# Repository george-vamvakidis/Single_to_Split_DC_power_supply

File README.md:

# Single_to_Split_DC_power_supply

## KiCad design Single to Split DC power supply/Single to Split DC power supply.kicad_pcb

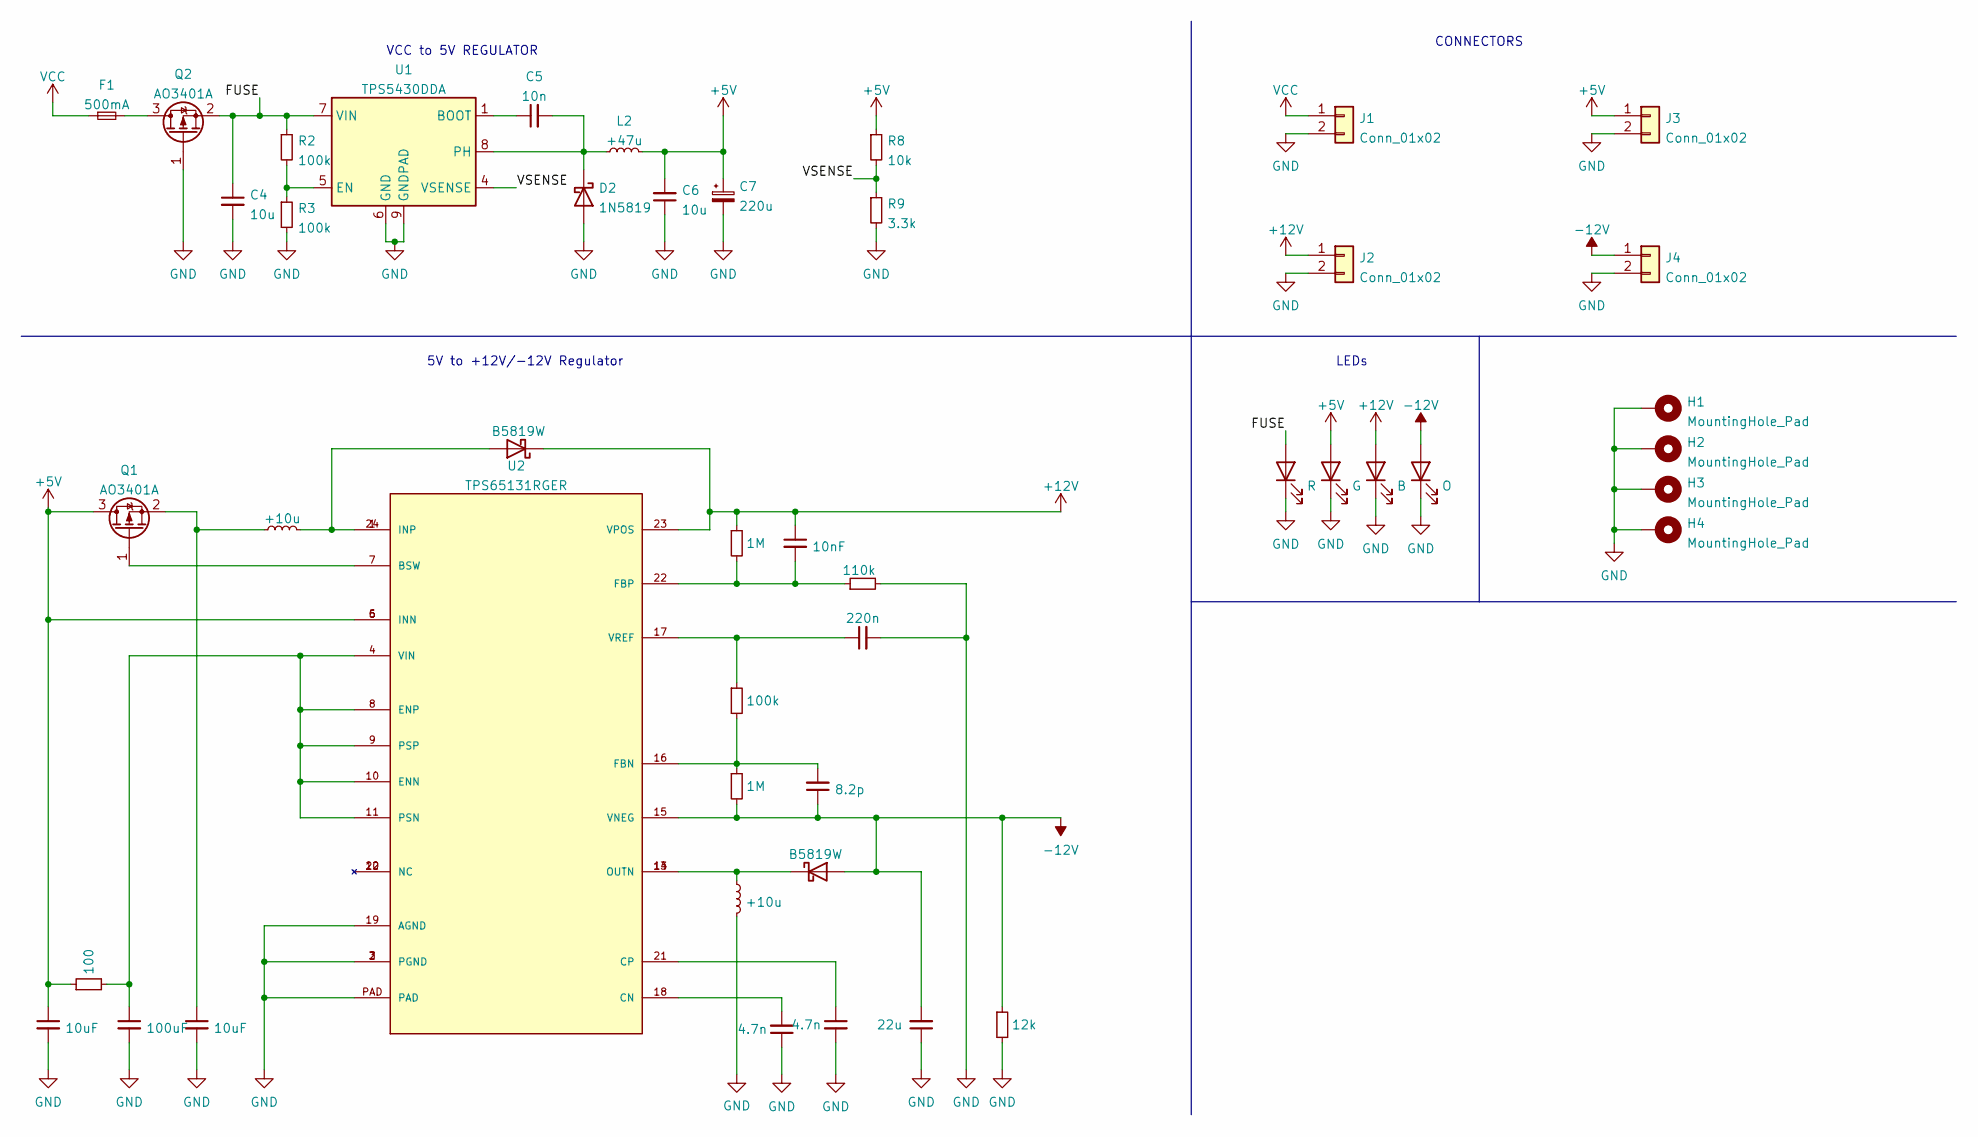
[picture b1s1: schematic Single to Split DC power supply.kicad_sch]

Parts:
C1, C3: 10uF; C_0603_1608Metric
C2: 100uF; C_0603_1608Metric
C4, C6: 10u; C_0603_1608Metric
C5: 10n; C_0603_1608Metric
C7: 220u; CP_Elec_4x5.4
C8, C11: 4.7n; C_0603_1608Metric
C9: 10nF; C_0603_1608Metric
C10: 8.2p; C_0603_1608Metric
C12: 220n; C_0603_1608Metric
C13: 22u; C_0603_1608Metric
D1, D3: B5819W; D_DO-41_SOD81_P10.16mm_Horizontal
D2: 1N5819; D_DO-41_SOD81_P10.16mm_Horizontal
D4: R; LED_1206_3216Metric
D5: G; LED_1206_3216Metric
D6: B; LED_1206_3216Metric
D7: O; LED_1206_3216Metric
F1: 500mA; SMDIP-4_W9.53mm
H1, H2, H3, H4: MountingHole_Pad; MountingHole_3.2mm_M3_Pad_Via
J1, J2, J3, J4: Conn_01x02; TerminalBlock_Altech_AK300-2_P5.00mm
L1, L3: +10u; L_1206_3216Metric
L2: +47u; L_1206_3216Metric
Q1, Q2: AO3401A; SOT-23
R1: 100; R_0603_1608Metric
R2, R3, R5: 100k; R_0603_1608Metric
R4, R6: 1M; R_0603_1608Metric
R7: 110k; R_0603_1608Metric
R8: 10k; R_0603_1608Metric
R9: 3.3k; R_0603_1608Metric
R10: 12k; R_0603_1608Metric
U1: TPS5430DDA; TI_SO-PowerPAD-8_ThermalVias
U2: TPS65131RGER; RGE0024B

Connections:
+5V: C1.1, C6.2, C7.1, D5.2 (A), J3.1, L2.2, Q1.3 (D), R1.1, R8.1, U2.5 (INN), U2.6 (INN)
+12V: C9.1, D1.1 (K), D6.2 (A), J2.1, R4.1, U2.23 (VPOS)
-12V: C10.1, C13.2, D3.2 (A), D7.2 (A), J4.1, R6.2, R10.1, U2.15 (VNEG)
/FUSE: C4.1, D4.2 (A), Q2.2 (S), R2.1, U1.7 (VIN)
/VSENSE: R8.2, R9.1, U1.4 (VSENSE)
GND: C1.2, C2.2, C3.2, C4.2, C6.1, C7.2, C8.1, C11.2, C12.2, C13.1, D2.2 (A), D4.1 (K), D5.1 (K), D6.1 (K), D7.1 (K), H1.1, H2.1, H3.1, H4.1, J1.2, J2.2, J3.2, J4.2, L3.2, Q2.1 (G), R3.2, R7.2, R9.2, R10.2, U1.6 (GND), U1.9 (GNDPAD), U2.2 (PGND), U2.3 (PGND), U2.19 (AGND), U2.PAD
unnamed: C2.1, R1.2, U2.4 (VIN), U2.8 (ENP), U2.9 (PSP), U2.10 (ENN), U2.11 (PSN)
unnamed: C3.1, L1.1, Q1.2 (S)
unnamed: C5.1, U1.1 (BOOT)
unnamed: C5.2, D2.1 (K), L2.1, U1.8 (PH)
unnamed: C8.2, U2.18 (CN)
unnamed: C9.2, R4.2, R7.1, U2.22 (FBP)
unnamed: C10.2, R5.2, R6.1, U2.16 (FBN)
unnamed: C11.1, U2.21 (CP)
unnamed: C12.1, R5.1, U2.17 (VREF)
unnamed: D1.2 (A), L1.2, U2.1 (INP), U2.24 (INP)
unnamed: D3.1 (K), L3.1, U2.13 (OUTN), U2.14 (OUTN)
unnamed: F1.2, Q2.3 (D)
unnamed: Q1.1 (G), U2.7 (BSW)
unnamed: R2.2, R3.1, U1.5 (EN)
VCC: F1.1, J1.1

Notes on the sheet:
LEDs
CONNECTORS
VCC to 5V REGULATOR
5V to +12V/-12V Regulator

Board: 2 copper layers, 46 parts (0 on the bottom side), 21 nets, no tracks yet.
